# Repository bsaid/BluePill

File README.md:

# BluePill

This project is a mess and it has never been tested.

The goal is to make STM32F103C BluePill compatible PCB with safety resistors, robust power supply with protections and SD card addon using a stacked PCB. The project is designed in [KiCad](https://www.kicad.org/) with design rules for [JLCPCB](https://jlcpcb.com/) including SMT assembly with their LCSC parts library.

This PCB was never tested or manufactured because the STM32 microcontrollers are out of stock globally.

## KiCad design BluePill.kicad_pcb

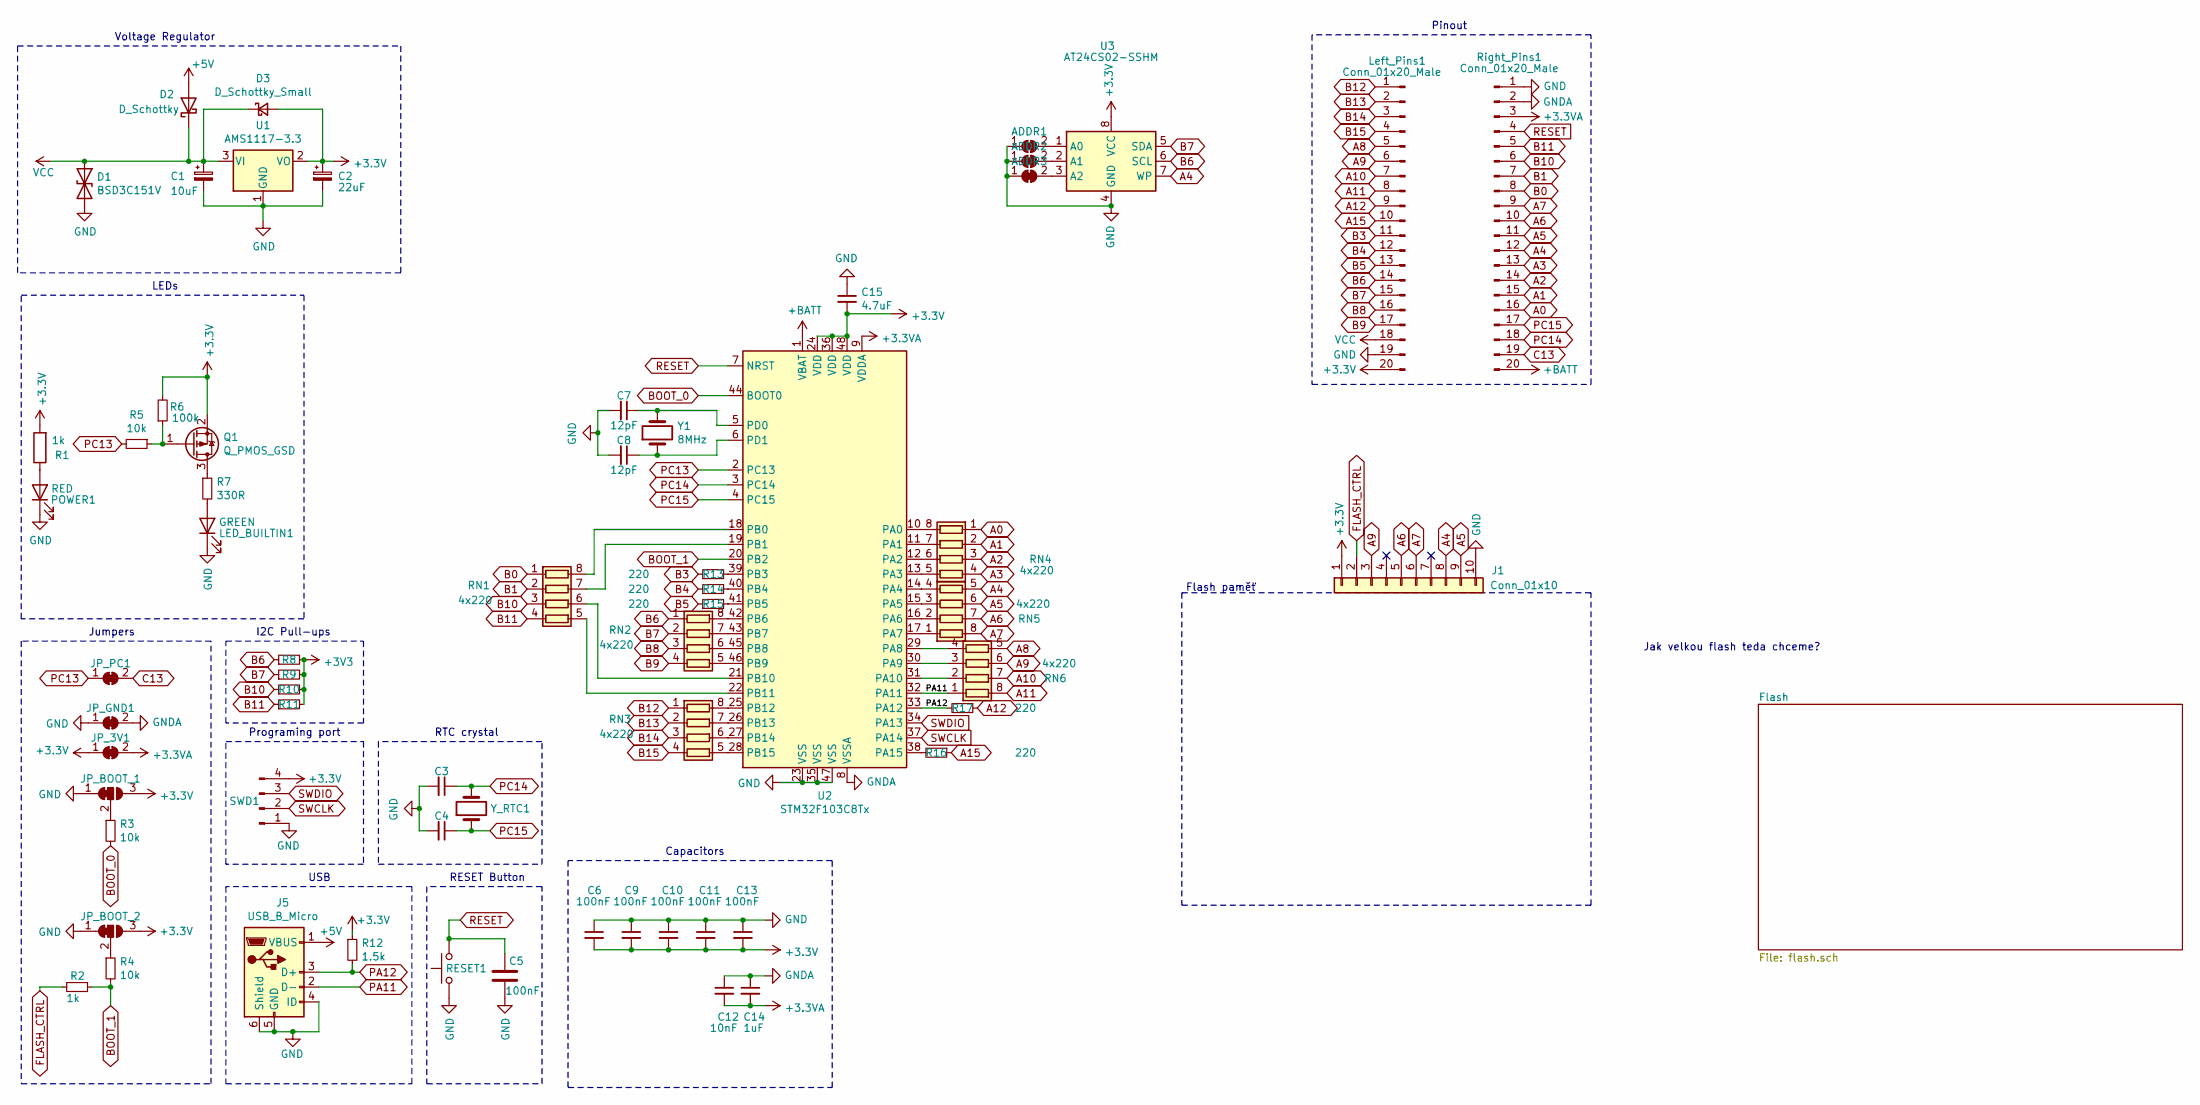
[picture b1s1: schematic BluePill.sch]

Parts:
ADDR1, ADDR2, ADDR3: GND; SolderJumper-2_P1.3mm_Bridged_RoundedPad1.0x1.5mm
C1: 10uF; CP_EIA-3216-18_Kemet-A; LCSC C117023
C2: 22uF; CP_EIA-2012-15_AVX-P; LCSC C11383
C3, C4: ?; C_0603_1608Metric_Pad1.08x0.95mm_HandSolder
C5, C6, C9, C10, C11, C13: 100nF; C_0402_1005Metric; LCSC C1525
C7, C8: 12pF; C_0402_1005Metric; LCSC C1547
C12: 10nF; C_0402_1005Metric; LCSC C15195
C14: 1uF; C_0402_1005Metric; LCSC C52923
C15: 4.7uF; C_0402_1005Metric; LCSC C23733
D1: BSD3C151V; R_1206_3216Metric_Pad1.30x1.75mm_HandSolder; LCSC C151990
D2: D_Schottky; D_SOD-323F; LCSC C78734
D3: D_Schottky_Small; DFN-2L_L1.0-W0.6-P0.65-RD; LCSC C134410
J1: Conn_01x10; Flash_connector
J5: USB_B_Micro; MICRO-USB-SMD_MICRO-USB-A11
JP_3V1: 3V3; SolderJumper-2_P1.3mm_Bridged_RoundedPad1.0x1.5mm
JP_BOOT_1: Boot 0; SolderJumper-3_P1.3mm_Bridged12_RoundedPad1.0x1.5mm
JP_BOOT_2: Boot 1; SolderJumper-3_P1.3mm_Bridged12_RoundedPad1.0x1.5mm
JP_GND1: GND; SolderJumper-2_P1.3mm_Bridged_RoundedPad1.0x1.5mm
JP_PC1: C13; SolderJumper-2_P1.3mm_Bridged_RoundedPad1.0x1.5mm
LED_BUILTIN1: GREEN; LED_0603_1608Metric; LCSC C72043
Left_Pins1: Conn_01x20_Male; PinHeader_1x20_P2.54mm_Vertical
POWER1: RED; LED_0603_1608Metric_Castellated; LCSC C2286
Q1: Q_PMOS_GSD; VBTA2245M; LCSC C692958
R1, R2: 1k; R_0402_1005Metric; LCSC C11702
R3, R4, R5: 10k; R_0402_1005Metric; LCSC C25744
R6: 100k; R_0402_1005Metric; LCSC C25741
R7: 330R; R_0402_1005Metric; LCSC C25104
R8, R9, R10, R11: ?; R_0603_1608Metric_Pad0.98x0.95mm_HandSolder
R12: 1.5k; R_0402_1005Metric; LCSC C25867
R13, R14, R15, R16, R17: 220; R_0402_1005Metric; LCSC C25091
RESET1: Reset; KEY-SMD_B3U-1000PM; LCSC C231329
RN1, RN2, RN3, RN4, RN5, RN6: 4x220; R_Array_Concave_4x0402; LCSC C25498
Right_Pins1: Conn_01x20_Male; PinHeader_1x20_P2.54mm_Vertical
SWD1: SWD; Harwin_M20-89004xx_1x04_P2.54mm_Horizontal
U1: AMS1117-3.3; SOT-223-3_TabPin2; LCSC C6186
U2: STM32F103C8Tx; LQFP-48_7x7mm_P0.5mm; LCSC C8734
U3: AT24CS02-SSHM; SOIC-8_3.9x4.9mm_P1.27mm
Y1: 8MHz; OSC-SMD_L5.0-W3.2; LCSC C156253
Y_RTC1: ?; Crystal_SMD_5032-2Pin_5.0x3.2mm_HandSoldering

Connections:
+3.3VA: C12.2, C14.2, JP_3V1.2 (B), Right_Pins1.3, U2.9 (VDDA)
+5V: D2.2 (A), J5.1 (VBUS)
+BATT: Right_Pins1.20, U2.1 (VBAT)
A0: RN4.1 (R1.1), Right_Pins1.16
A1: RN4.2 (R2.1), Right_Pins1.15
A2: RN4.3 (R3.1), Right_Pins1.14
A3: RN4.4 (R4.1), Right_Pins1.13
A4: J1.8, RN5.5 (R4.2), Right_Pins1.12, U3.7 (WP)
A5: J1.9, RN5.6 (R3.2), Right_Pins1.11
A6: J1.5, RN5.7 (R2.2), Right_Pins1.10
A7: J1.6, RN5.8 (R1.2), Right_Pins1.9
A8: Left_Pins1.5, RN6.5 (R4.2)
A9: J1.3, Left_Pins1.6, RN6.6 (R3.2)
A10: Left_Pins1.7, RN6.7 (R2.2)
A11: Left_Pins1.8, RN6.8 (R1.2)
A12: Left_Pins1.9, R17.1
A15: Left_Pins1.10, R16.1
B0: RN1.1 (R1.1), Right_Pins1.8
B1: RN1.2 (R2.1), Right_Pins1.7
B3: Left_Pins1.11, R13.1
B4: Left_Pins1.12, R14.1
B5: Left_Pins1.13, R15.1
B6: Left_Pins1.14, R8.1, RN2.1 (R1.1), U3.6 (SCL)
B7: Left_Pins1.15, R9.1, RN2.2 (R2.1), U3.5 (SDA)
B8: Left_Pins1.16, RN2.3 (R3.1)
B9: Left_Pins1.17, RN2.4 (R4.1)
B10: R10.1, RN1.3 (R3.1), Right_Pins1.6
B11: R11.1, RN1.4 (R4.1), Right_Pins1.5
B12: Left_Pins1.1, RN3.1 (R1.1)
B13: Left_Pins1.2, RN3.2 (R2.1)
B14: Left_Pins1.3, RN3.3 (R3.1)
B15: Left_Pins1.4, RN3.4 (R4.1)
BOOT_0: R3.2, U2.44 (BOOT0)
BOOT_1: R2.1, R4.2, U2.20 (PB2)
C13: JP_PC1.2 (B), Right_Pins1.19
FLASH_CTRL: J1.2, R2.2
GND: ADDR1.1 (A), ADDR2.1 (A), ADDR3.1 (A), C1.2, C2.2, C3.2, C4.2, C5.1, C6.1, C7.2, C8.2, C9.1, C10.1, C11.1, C13.1, C15.1, D1.2 (A2), J1.10, J5.4 (ID), J5.5 (GND), J5.6 (Shield), JP_BOOT_1.1 (A), JP_BOOT_2.1 (A), JP_GND1.1 (A), LED_BUILTIN1.1 (K), Left_Pins1.19, POWER1.1 (K), RESET1.1, Right_Pins1.1, SWD1.1, U1.1 (GND), U2.23 (VSS), U2.35 (VSS), U2.47 (VSS), U3.4 (GND)
GNDA: C12.1, C14.1, JP_GND1.2 (B), Right_Pins1.2, U2.8 (VSSA)
unnamed: ADDR1.2 (B), U3.1 (A0)
unnamed: ADDR2.2 (B), U3.2 (A1)
unnamed: ADDR3.2 (B), U3.3 (A2)
unnamed: C7.1, U2.5 (PD0), Y1.2
unnamed: C8.1, U2.6 (PD1), Y1.1
unnamed: JP_BOOT_1.2 (C), R3.1
unnamed: JP_BOOT_2.2 (C), R4.1
unnamed: LED_BUILTIN1.2 (A), R7.2
unnamed: POWER1.2 (A), R1.1
unnamed: Q1.1 (G), R5.1, R6.1
unnamed: Q1.3 (D), R7.1
unnamed: R13.2, U2.39 (PB3)
unnamed: R14.2, U2.40 (PB4)
unnamed: R15.2, U2.41 (PB5)
unnamed: R16.2, U2.38 (PA15)
unnamed: RN1.5 (R4.2), U2.22 (PB11)
unnamed: RN1.6 (R3.2), U2.21 (PB10)
unnamed: RN1.7 (R2.2), U2.19 (PB1)
unnamed: RN1.8 (R1.2), U2.18 (PB0)
unnamed: RN2.5 (R4.2), U2.46 (PB9)
unnamed: RN2.6 (R3.2), U2.45 (PB8)
unnamed: RN2.7 (R2.2), U2.43 (PB7)
unnamed: RN2.8 (R1.2), U2.42 (PB6)
unnamed: RN3.5 (R4.2), U2.28 (PB15)
unnamed: RN3.6 (R3.2), U2.27 (PB14)
unnamed: RN3.7 (R2.2), U2.26 (PB13)
unnamed: RN3.8 (R1.2), U2.25 (PB12)
unnamed: RN4.5 (R4.2), U2.13 (PA3)
unnamed: RN4.6 (R3.2), U2.12 (PA2)
unnamed: RN4.7 (R2.2), U2.11 (PA1)
unnamed: RN4.8 (R1.2), U2.10 (PA0)
unnamed: RN5.1 (R1.1), U2.17 (PA7)
unnamed: RN5.2 (R2.1), U2.16 (PA6)
unnamed: RN5.3 (R3.1), U2.15 (PA5)
unnamed: RN5.4 (R4.1), U2.14 (PA4)
unnamed: RN6.2 (R2.1), U2.31 (PA10)
unnamed: RN6.3 (R3.1), U2.30 (PA9)
unnamed: RN6.4 (R4.1), U2.29 (PA8)
PA11: J5.2 (D-), RN6.1 (R1.1), U2.32 (PA11)
PA12: J5.3 (D+), R12.2, R17.2, U2.33 (PA12)
PC13: JP_PC1.1 (A), R5.2, U2.2 (PC13)
PC14: C3.1, Right_Pins1.18, U2.3 (PC14), Y_RTC1.2
PC15: C4.1, Right_Pins1.17, U2.4 (PC15), Y_RTC1.1
RESET: C5.2, RESET1.2, Right_Pins1.4, U2.7 (NRST)
SWCLK: SWD1.2, U2.37 (PA14)
SWDIO: SWD1.3, U2.34 (PA13)
VCC: C1.1, D1.1 (A1), D2.1 (K), D3.1 (K), Left_Pins1.18, U1.3 (VI)

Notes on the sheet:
Jumpers
I2C Pull-ups
Programing port
USB
LEDs
RESET Button
Pinout
Voltage Regulator
Flash paměť
Capacitors
RTC crystal
Jak velkou flash teda chceme?

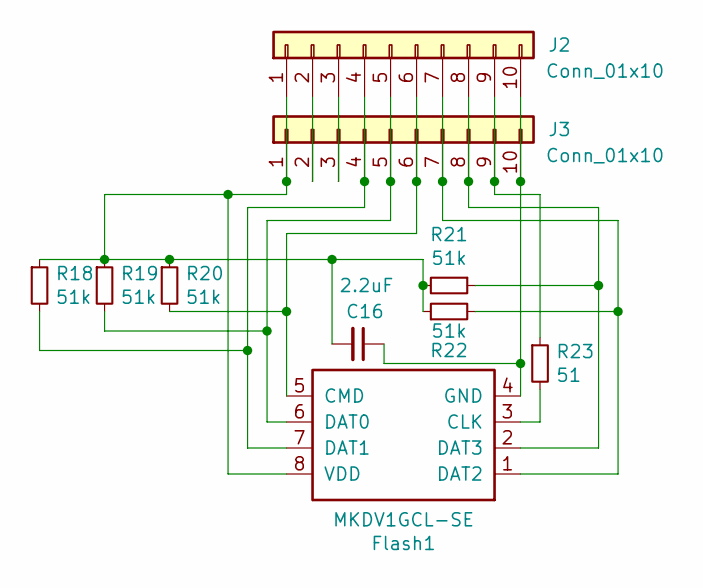
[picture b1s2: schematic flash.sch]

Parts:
C16: 2.2uF; C_0402_1005Metric; LCSC C12530
Flash1: MKDV1GCL-SE; LGA-8_L6.0-W8.0-P1.27-TL
J2: Conn_01x10; Flash_connector_2
J3: Conn_01x10; Flash_connector
R18, R19, R20, R21, R22: 51k; R_0402_1005Metric; LCSC C25794
R23: 51; R_0402_1005Metric; LCSC C25125

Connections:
unnamed: C16.1, Flash1.4 (GND), J2.10, J3.10
unnamed: C16.2, Flash1.8 (VDD), J2.1, J3.1, R18.1, R19.1, R20.1, R21.2, R22.1
unnamed: Flash1.1 (DAT2), J2.7, J3.7, R22.2
unnamed: Flash1.2 (DAT3), J2.8, J3.8, R21.1
unnamed: Flash1.3 (CLK), R23.2
unnamed: Flash1.5 (CMD), J2.6, J3.6, R20.2
unnamed: Flash1.6 (DAT0), J2.5, J3.5, R19.2
unnamed: Flash1.7 (DAT1), J2.4, J3.4, R18.2
unnamed: J2.2, J3.2
unnamed: J2.3, J3.3
unnamed: J2.9, J3.9, R23.1

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
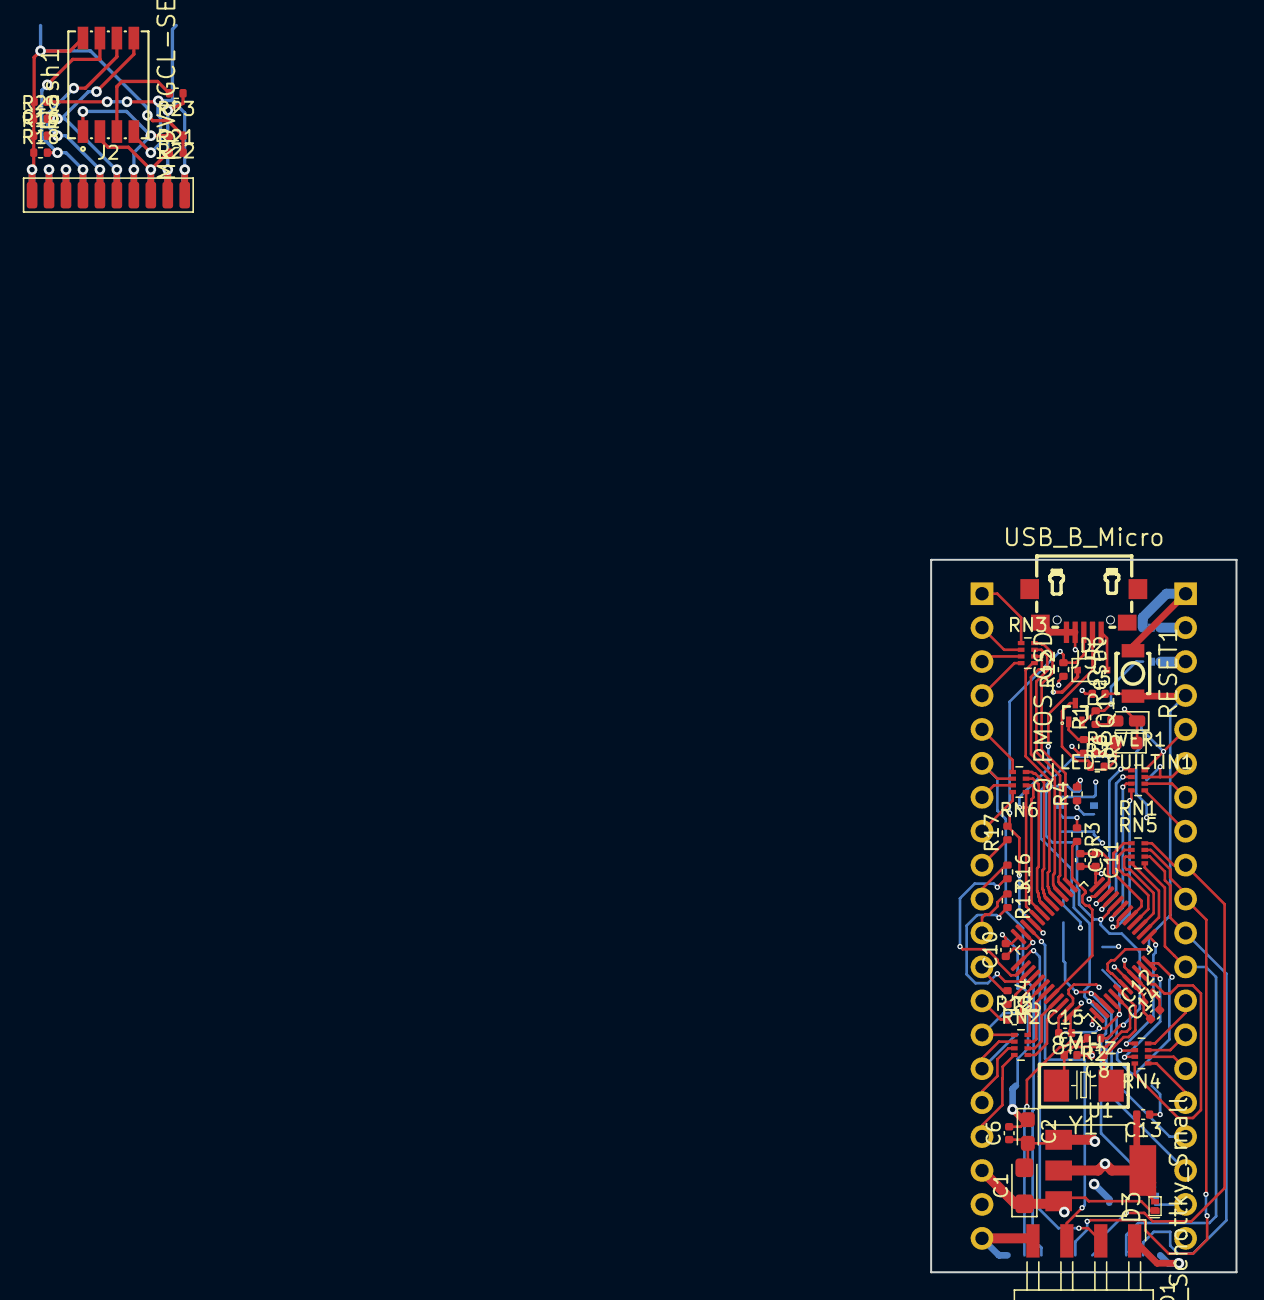
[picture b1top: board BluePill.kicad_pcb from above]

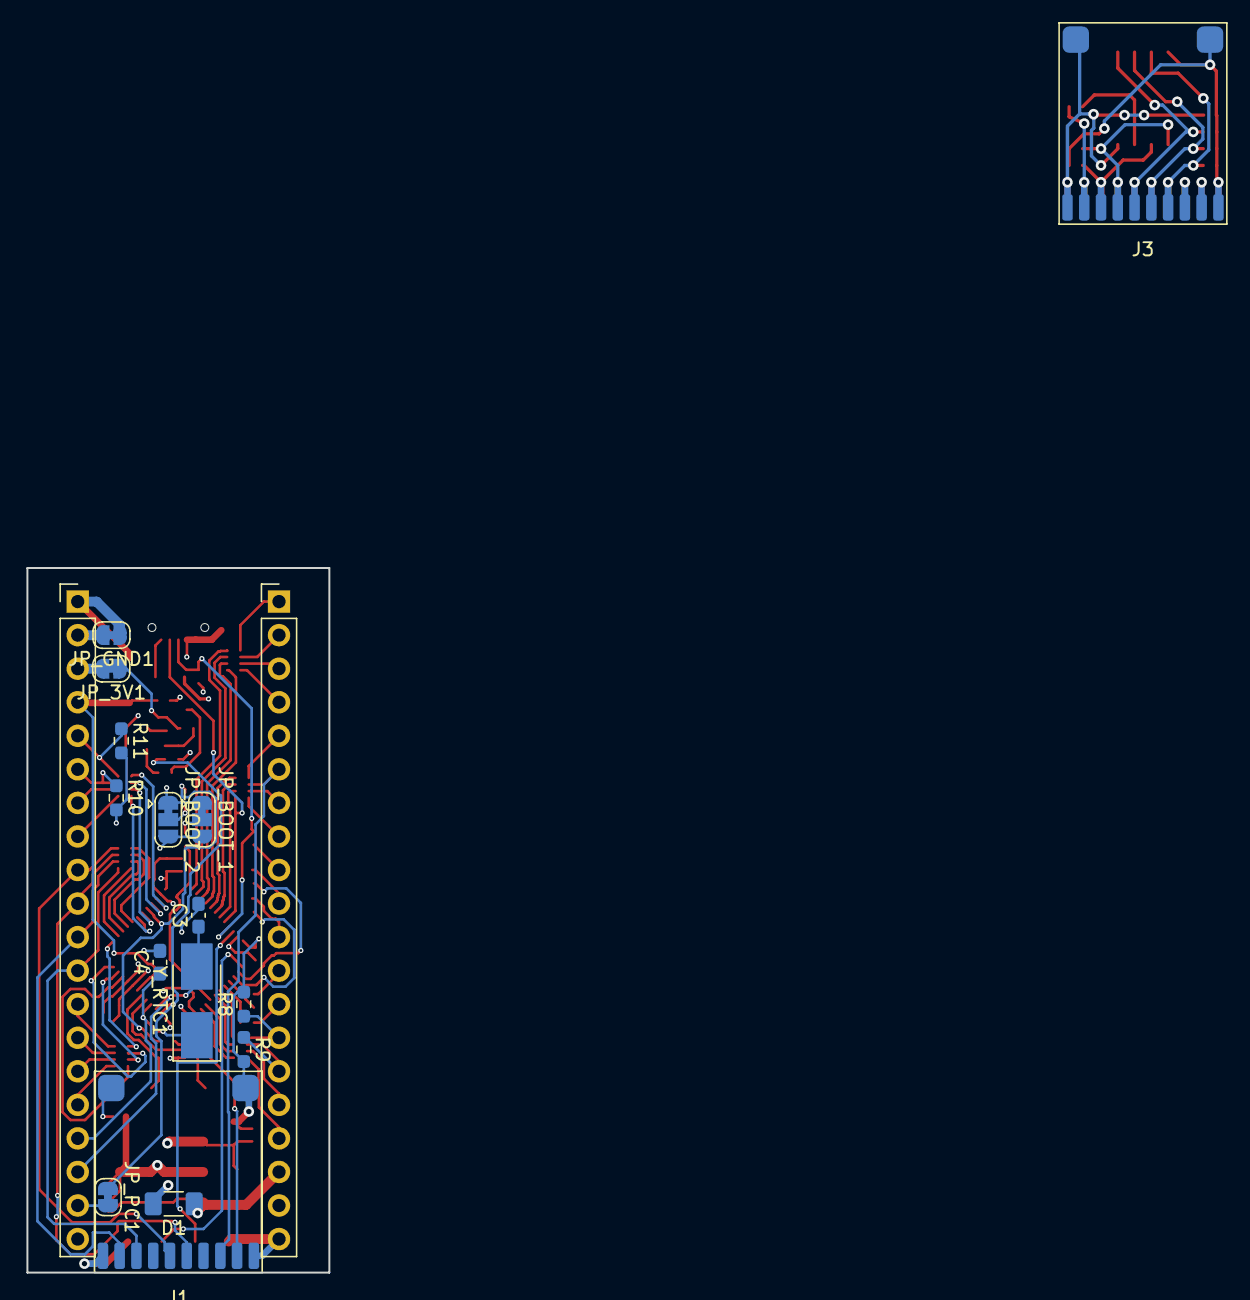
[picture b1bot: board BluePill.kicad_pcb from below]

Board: 4 copper layers, 22.9 x 53.3 mm, 69 parts (17 on the bottom side), 94 nets.

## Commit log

2020-09-12 Initial commit.
2020-09-16 Fix some warnings
2020-09-17 Generate cam
2020-09-19 Add paneled version
2020-09-19 Finish panelized version
2020-09-19 Generate new gerber files
2021-03-02 Switch to KiCad
2021-03-21 Finish schematic
2021-03-21 Add LCSC numbers
2021-03-23 Route board
2022-04-08 Added 3D render of the PCB.
